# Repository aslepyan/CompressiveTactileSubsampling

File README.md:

<div align="center">

# Adaptive Compressive Tactile Subsampling: Enabling High Spatiotemporal Resolution in Scalable Robotic Skin

[[Paper](https://arxiv.org/abs/2410.13847)]

[Ariel Slepyan](https://scholar.google.com/citations?hl=en&user=8uVwi4UAAAAJ&view_op=list_works&sortby=pubdate)<sup>1</sup>†, 
[Dian Li (李典)](https://scholar.google.com/citations?view_op=list_works&hl=en&user=L_5PIfgAAAAJ)<sup>2</sup>†, 
[Hongjun Cai](mailto:hcai18@jh.edu)<sup>1</sup>, 
[Ryan McGovern](https://scholar.google.com/citations?user=T1UDhk8AAAAJ&hl=en&oi=ao)<sup>2</sup>, 
[Aidan Aug](https://www.researchgate.net/profile/Aidan_Aug)<sup>2</sup>, 
[Sriramana Sankar](https://scholar.google.com/citations?user=SCZ0ibcAAAAJ&hl=en)<sup>2</sup>, 
[Trac Tran](https://scholar.google.com/citations?user=RyRjA0cAAAAJ&hl=en)<sup>1</sup>, 
[Nitish Thakor](https://scholar.google.com/citations?user=SB_7Bi0AAAAJ&hl=en)<sup>1,2,3</sup>
<br />
<sup>1</sup> Department of Electrical and Computer Engineering, Johns Hopkins University, Baltimore, USA<br />
<sup>2</sup> Department of Biomedical Engineering, Johns Hopkins School of Medicine, Baltimore, USA<br />
<sup>3</sup> Department of Neurology, Johns Hopkins School of Medicine, Baltimore, USA<br />
†These authors contributed equally to this study.
</div>

## Usage
The codes for using our methods for tactile image data and realizing our results are explained below. Notice that you can access our data files through this 
[link](https://livejohnshopkins-my.sharepoint.com/:f:/g/personal/aslepya1_jh_edu/EjxrHBfSJDROho7Z2A9AB-YBggjp6DtikdrMtPDEytMRLw?e=0MTquj). 
Some helper functions are not described here, but you can check the comments about their usage in the corresponding files. <br />
The folder `ksvdbox13` for training ksvd dictionary could be downloaded [here](https://csaws.cs.technion.ac.il/~ronrubin/software.html). This folder should be placed at `code\`.

### Data folders
Download each data folder and put it into the directory `data\`. Each data folder is explained below.
* `Subsampling_Data` is for 30 daily objects;
* `Projectile_Data` is for the application of detecting a bouncing tennis ball;
* `ricochet_angle_data` stores data of a bouncing tennis ball with specific incidence angles.
* `Deformation_Data` is for the application of detecting deformable objects;
* `manikin_data` stores data for slashing, shooting, and punching a manikin;
* `robot_data` stores data for slashing and pulling a UR5 robot arm;
* `insole_data` is for recording jumping;
* `arm_data` is for tapping on an arm;
* `chest_data` is for touching a chest;
* `helmet_data` is for the impact of foam bullet on a helmet;
* `leg_data` is for bouncing a ball on a leg;
* `glove_data` is for catching and throwing a tennis ball with a hand worn by a glove;
* `Rotator_Data` is for the application of the rotator;
* `Demo_Data` stores data for the video demonstration;
* `archieveData` is used to store useful data files for subsequent data analysis, such as accuracy determination of reconstruction and sparse representation classification (SRC);
* `traningData` is used to store various dictionaries and their auxiliary data, training data sets, and an SRC library.

### Hardware
The PCB design files are located in the `PCB` folder. These files are designed in KiCAD and contain the schematic and layout for readout board (`PCB Files Readout Board`) and the 32x32 tactile sensor array (`PCB Files Tactile Sensor Array`).

### Subsampled Data Acquisition
If you want to collect some tactile data in a subsampling manner, use the folder `code\data_collection\`. To sample tactile data, upload `Subsampling.ino` to the sensor after adjusting the parameters. After that, run `SubsamplingControl.m` with desirable parameters to sample data using various methods.
* `Subsampling` contains the Arduino code used to enable the sensor to execute subsampling tactile data within a designated duration; The sampling process is initiated by touching;
* `Subsampling1` contains the Arduino code used to enable the sensor to execute subsampling tactile data within a designated duration; The sampling process is initiated by the `Enter` key;
* `SubsamplingControl.m` is the main function for subsampling in three different modes: regular, random, and binary;
* `downSamplingShift.m`, `randomSampling.m` and `binarySampling.m` are functions for regular, random, and binary sampling methods, respectively; The sampling process is initiated by touching;
* `randomSampling1.m` and `binarySampling1.m` are functions for random and binary sampling methods, respectively; The sampling process is initiated by the `Enter` key;
* `SubsamplingDisplay.m` is used to visualize the subsampled tactile image;
* `M_fs_plot.m` plots the relation between the sampling rate and the measurement level;
* `time_force.m` makes a time-force plot.

### Tactile Dictionary Training
The folder `code\dict_training\` is for the task of training dictionary, it allows to train three types of dictionary: learned dictionary, DCT dictionary and Haar dictionary (square and overcomplete). You can acquire all types of dictionaries by running the following corresponding files. If you want to recover subsampled images as a whole,  run `dictCombine.m` to get the assembled dictionaries for the whole subsampled images.
* `trainData.m` is responsible for collecting the training data and its last section is to visualize the full raster tactile image you collected.
* `dictTraining_ksvd.m` is for training the learned dictionary based on your training data;
* `dictTraining_DCT.m` is used to train the DCT dictionary;
* `dictTraining_overcompleteHaar.m` is used to train the Haar dictionary;
* `dictCombine.m` combines several patch dictionaries together to recover subsampled tactile images as a whole.

### Subsampled Image Recovery
The folder `code\reconstruction` is for the reconstruction of collected subsampled tactile data. First, recover the subsampled data using various methods (dictionaries or interpolation) by running the following MATLAB files. Then, you can check the reconstructed images using the file `recDataDisplay.m`. Last, run `reconAccPlot.m` to calculate the accuracies of the reconstructed images and plot some relevant figures shown in the paper.
* `dictRecovery.m` is used to reconstruct the tactile image patch by patch by using various types of dictionaries;
* `interpRecovery.m` is used to reconstruct the tactile image by using linear interpolation;
* `recDataDisplay.m` is used to view the reconstructed subsampled image;
* `reconAccPlot.m` is used to calculate the accuracies of the reconstructed images and plot some relevant figures. Here, the objects used to do the subsampling have also been used to train the learned dictionary for subsampled image recovery.

### Subsampled Image Classification
The folder `code\classification` is for the classification of collected subsampled tactile data. Firstly, run `libTraining.m` to acquire the library for SRC. Then, run each section of `SRC.m` to conduct SRC, calculate accuracies or realize some figures in the paper. Besides, the code for the visualization of the library is also provided. Here, the objects used for subsampling have also been used to form the library for subsampled image classification.
* `libTraining.m` is used to construct a library for SRC and visualize the library;
* `SRC.m` is used to determine the classes the reconstructed images belong to, calculate the accuracies of the classification of different sampling modes and measurement levels, and plot some relevant figures.

### Real-time Full Raster Scan
The folder `code\realTimeFR\` is to visualize a real-time full raster scan of the sensor. First, upload `realTimeFR_32x32.ino` and then run `realTimeFR_32x32.m`.

## Applications
With the proposed sampling modes, reconstruction using a learned dictionary, and SRC, we have designed and conducted several experiments to investigate their feasibility and accuracy. Here, we explain the folders and files for these experiments.

### Projectile
The folder `code\projectile` is for the application of fast detection of a tennis ball (as a projectile) onto the sensor. Firstly, you can directly use our data, or you need to collect the tactile images of the bouncing tennis ball by using the file `SubsamplingControl.m` with the binary subsampling mode. Then, run each section of `projectileAnalysis.m` and `instant_angle.m` to process the projectile's subsampled data and plot the figures shown in the paper.
* `projectileAnalysis.m` analyzes the projectile's subsampled data and generates some figures;
* `instant_angle.m` is the main code for this demo of tracking the instant angle of incidence of a bouncing ball.

### Deformation
The folder `code\deform` is for the application of roughly drawing the shape of deformable objects. Firstly, you can directly use our data, or you need to collect the tactile images of some deformable objects (e.g. deflated balloon or elastic objects) by using the file `SubsamplingControl.m` with the binary subsampling mode. Then, run each section of `deformAnalysis.m` to process the subsampled data of those deformable objects and draw their rough shape, as shown in the paper.
* `deformAnalysis.m` analyzes the subsampled data of deformable objects and generates a figure depicting their approximate shapes.

### Full-Body Tactile Sensing
* `code\reconstruction\recDataDisplay.m` could also be used to check the subsampled and reconstructed tactile data collected from insole, chest, helmet, glove, leg, and arm.

### Real-time Reconstruction and Classification
The folder `code\realTime` is for the application of real-time reconstruction or classification without any data processing outside the sensor.<br />
To realize the real-time reconstruction, firstly, you need to have a reasonably learned dictionary using the K-SVD method. After adjusting some parameters, you need to upload the `realTimeBinaryReconPBP.ino` to the sensor. Then, run the `helperMat.m` and `dict2Arduino_recon.m` to transfer the dictionary and its helper matrices to the sensor. Finally, you can visualize the real-time tactile images by using `realTimeVis.m`.<br />
For its simulation, you need to upload the file named `realTimeBinaryReconPBP.ino` and determine the accuracy by using the `realTimeSimu.m`, while all the remaining operations are the same as the real-time reconstruction.<br />
As for the real-time classification, first of all, you need get the library through `libTraining.m` as mentioned above. After adjusting some parameters, upload the `realTimeBinarySRC.ino` to the sensor. Then, run the `dict2Arduino_class.m` to transfer the library to the sensor. Last, visualize the real-time classification through the serial monitor in the Arduino.
* `realTimeBinaryReconPBP` contains the Arduino code to enable the sensor to sample the tactile data in real-time by using the binary subsampling method, and to reconstruct the subsampled image by a learned dictionary patch by patch;
* `realTimeBinaryReconPBPSimu` contains the Arduino code to enable the sensor to sample and reconstruct the full raster tactile data, which has been sampled and stored. This simulation aims to determine the accuracy of the real-time reconstruction method by a learned dictionary patch by patch;
* `realTimeBinarySRC` contains the Arduino code to enable the sensor to sample the tactile data in real-time using the binary subsampling method, and to classify the subsampled tactile image using the SRC method;
* `realTimeBinarySRCSimu` contains the Arduino code to enable the sensor to sample and classify the full raster tactile data, which has been sampled and stored. This simulation aims to determine the accuracy of the real-time classification by SRC;
* `dict2Arduino_recon.m` is used to transfer a learned dictionary and its corresponding helper matrices from MATLAB to the sensor;
* `dict2Arduino_class.m` is used to transfer a library used in the SRC from MATLAB to the sensor;
* `helperMat.m` is used to determine and store the helper matrices according to the learned dictionary which will be used in the real-time reconstruction later;
* `realTimeVis.m` is used to visualize the real-time reconstruction;
* `realTimeReconSimu.m` is used to determine the accuracy of reconstruction of full-raster tactile images in the simulation;
* `realTimeSRCSimu.m` is used to determine the accuracy of classification of full-raster tactile images in the simulation;
* `realTimePlot.m` is used to plot all relevant figures related to this application. 

## Supplements
The folder `code\supplements` contains the file that generates some results shown in the supplementary file.
* `rot.m` analyzes the subsampled data of a hard rotator at different speeds (or frequencies) and generates the single-sided amplitude spectrums.
* `forceR.m` determines the relationship between the force applied to the sensor and its measurement/resistance;
* `downSamOrd.m` visualizes consecutive shifting down-sampling patterns;
* `binSamOrd` simulates and determines the order of binary sampling, given a number of sensors and a simple press image (where non-zero presses exist);
* `binSamOrd.m` visualizes a binary sampling pattern determined by params in `binSamOrd`;
* `genReconAccPlot.m` calculates the accuracies of the reconstructed images from objects that are not used to train a learned dictionary and plots some relevant figures shown in the paper.

## Citation
```
    @article{,
      author    = {Ariel Slepyan and Dian Li and Aidan Aug and Sriramana Sankar and Trac Tran and Nitish Thakor},
      title     = {Adaptive Subsampling and Learned Model Improve Spatiotemporal Resolution of Tactile Skin},
      journal   = {arXiv preprint arXiv:2410.13847},
      year      = {2024},
      url       = {https://arxiv.org/abs/2410.13847}
    }
```

## Acknowledgement
We sincerely appreciate Prof. Jeremy Brown for his advice on this work. We also many many thanks Dr. Ron Rubinstein for his code for training the ksvd dictionary.

## Contact
If you have any questions or inquiries, please feel free to contact this [email](mailto:dli106@jhmi.edu).

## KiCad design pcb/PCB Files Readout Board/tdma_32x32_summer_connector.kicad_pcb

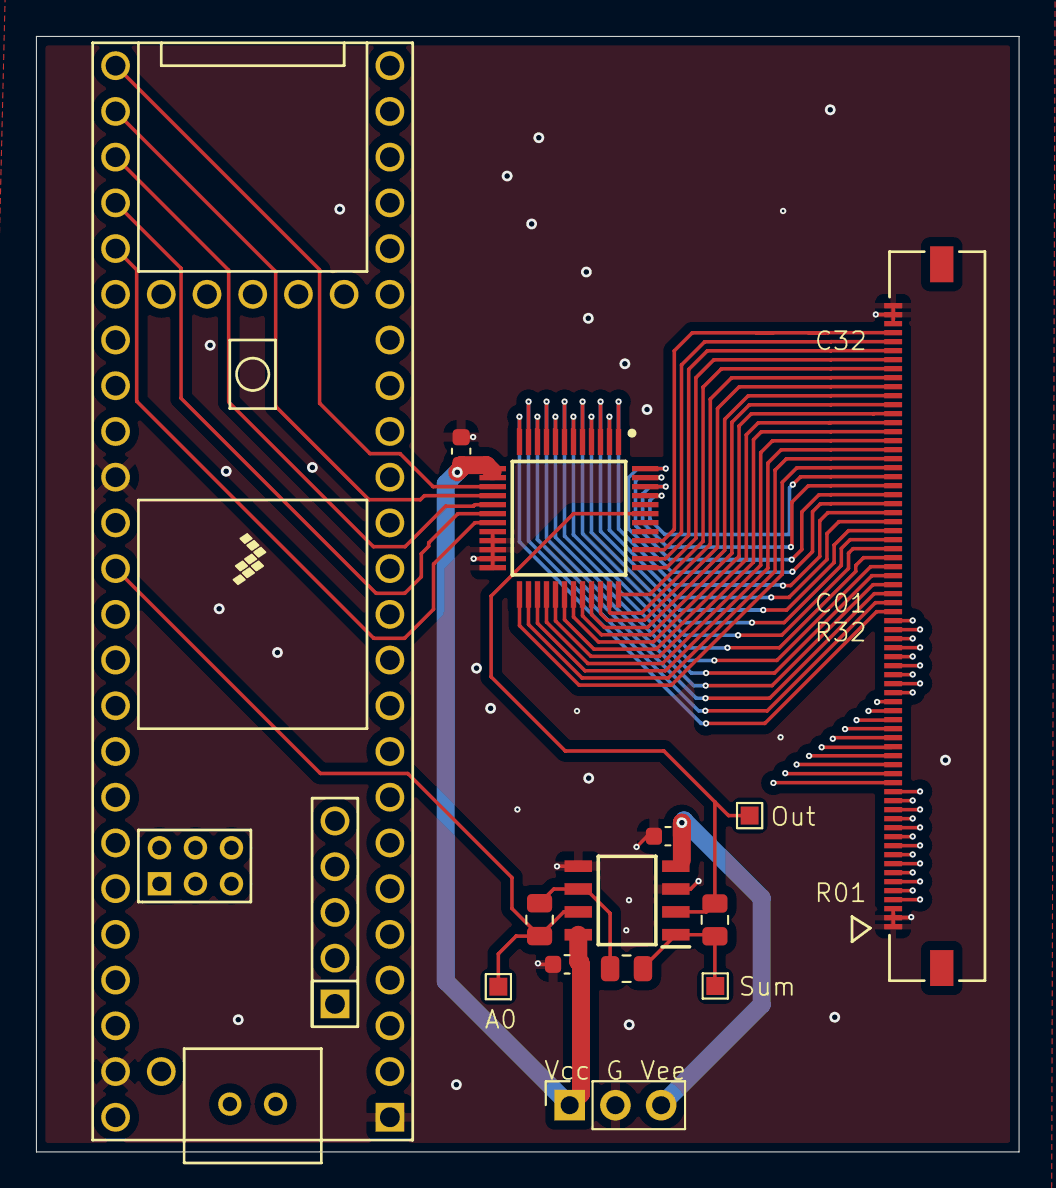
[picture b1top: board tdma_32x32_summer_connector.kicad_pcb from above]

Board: 4 copper layers, 54.6 x 62.0 mm, 14 parts (0 on the bottom side), 76 nets.

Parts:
C1, C3, C4: C; C_0603_1608Metric
IC1: ADG732BSUZ; QFP50P900X900X120-48N
IC2: LM358BAIDR; SOIC127P600X175-8N
J2: Conn_01x03_Pin; PinSocket_1x03_P2.54mm_Vertical
J3: 5051107091
R1, R2, R3: R; R_0805_2012Metric
TP1, TP2, TP3: TestPoint; TestPoint_Pad_1.0x1.0mm
U1: Teensy4.1; Teensy41

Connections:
A0: IC2.7 (OUT2), R3.1, TP3.1, U1.36 (14_A0_TX3_SPDIF_OUT)
GND: C1.2, C3.2, C4.2, IC1.20 (~CS), IC1.21 (~WR), IC1.22 (~EN), IC1.23 (GND), IC1.24 (VSS), IC2.3 (IN1+), IC2.5 (IN2+), J2.2, J3.1, J3.2, J3.3, J3.68, J3.69, J3.70, U1.1 (GND), U1.34 (GND), U1.47 (GND), U1.52 (GND)
unnamed: IC2.6 (IN2-), R2.2, R3.2
unnamed: IC2.1 (OUT1), R1.2, R2.1, TP2.1
VCC: C1.1, C4.1, IC1.13 (VDD_1), IC1.14 (VDD_2), IC2.8 (V+), J2.1
VEE: C3.1, IC2.4 (V-), J2.3
c1: IC1.12 (S1), J3.36
c2: IC1.11 (S2), J3.37
c3: IC1.10 (S3), J3.38
c4: IC1.9 (S4), J3.39
c5: IC1.8 (S5), J3.40
c6: IC1.7 (S6), J3.41
c7: IC1.6 (S7), J3.42
c8: IC1.5 (S8), J3.43
c9: IC1.4 (S9), J3.44
c10: IC1.3 (S10), J3.45
c11: IC1.2 (S11), J3.46
c12: IC1.1 (S12), J3.47
c13: IC1.48 (S13), J3.48
c14: IC1.47 (S14), J3.49
c15: IC1.46 (S15), J3.50
c16: IC1.45 (S16), J3.51
c17: IC1.25 (S17), J3.52
c18: IC1.26 (S18), J3.53
c19: IC1.27 (S19), J3.54
c20: IC1.28 (S20), J3.55
c21: IC1.29 (S21), J3.56
c22: IC1.30 (S22), J3.57
c23: IC1.31 (S23), J3.58
c24: IC1.32 (S24), J3.59
c25: IC1.33 (S25), J3.60
c26: IC1.34 (S26), J3.61
c27: IC1.35 (S27), J3.62
c28: IC1.36 (S28), J3.63
c29: IC1.37 (S29), J3.64
c30: IC1.38 (S30), J3.65
c31: IC1.39 (S31), J3.66
c32: IC1.40 (S32), J3.67
mux0: IC1.15 (A0), U1.25 (33_MCLK2)
mux1: IC1.16 (A1), U1.26 (34_RX8)
mux2: IC1.17 (A2), U1.27 (35_TX8)
mux3: IC1.18 (A3), U1.28 (36_CS)
mux4: IC1.19 (A4), U1.29 (37_CS)
out: IC1.43 (D), IC2.2 (IN1-), R1.1, TP1.1
r1: J3.4, U1.2 (0_RX1_CRX2_CS1)
r2: J3.5, U1.3 (1_TX1_CTX2_MISO1)
r3: J3.6, U1.4 (2_OUT2)
r4: J3.7, U1.5 (3_LRCLK2)
r5: J3.8, U1.6 (4_BCLK2)
r6: J3.9, U1.7 (5_IN2)
r7: J3.10, U1.8 (6_OUT1D)
r8: J3.11, U1.9 (7_RX2_OUT1A)
r9: J3.12, U1.10 (8_TX2_IN1)
r10: J3.13, U1.11 (9_OUT1C)
r11: J3.14, U1.12 (10_CS_MQSR)
r12: J3.15, U1.13 (11_MOSI_CTX1)
r13: J3.16, U1.14 (12_MISO_MQSL)
r14: J3.17, U1.35 (13_SCK_LED)
r15: J3.18, U1.37 (15_A1_RX3_SPDIF_IN)
r16: J3.19, U1.38 (16_A2_RX4_SCL1)
r17: J3.20, U1.39 (17_A3_TX4_SDA1)
r18: J3.21, U1.40 (18_A4_SDA)
r19: J3.22, U1.41 (19_A5_SCL)
r20: J3.23, U1.42 (20_A6_TX5_LRCLK1)
r21: J3.24, U1.43 (21_A7_RX5_BCLK1)
r22: J3.25, U1.44 (22_A8_CTX1)
r23: J3.26, U1.45 (23_A9_CRX1_MCLK1)
r24: J3.27, U1.16 (24_A10_TX6_SCL2)
r25: J3.28, U1.17 (25_A11_RX6_SDA2)
r26: J3.29, U1.18 (26_A12_MOSI1)
r27: J3.30, U1.19 (27_A13_SCK1)
r28: J3.31, U1.20 (28_RX7)
r29: J3.32, U1.21 (29_TX7)
r30: J3.33, U1.22 (30_CRX3)
r31: J3.34, U1.23 (31_CTX3)
r32: J3.35, U1.24 (32_OUT1B)

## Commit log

2024-09-18 pcb files
2024-10-01 Create s
2024-10-09 Create w
2024-11-01 Create code
2024-12-19 Rename instruction.md to data/instruction.md
2024-12-19 Rename instruction.md to instruction.txt
2025-03-23 Update README.md
    Acknowledgment
